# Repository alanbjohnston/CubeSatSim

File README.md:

# CubeSatSim

The CubeSat Simulator https://github.com/alanbjohnston/CubeSatSim/wiki is a low cost satellite emulator that runs on solar panels and batteries, transmits UHF radio telemetry, has a 3D printed frame, and can be extended by additional sensors and modules.  This project is sponsored by the not-for-profit [Radio Amateur Satellite Corporation, AMSAT®](https://amsat.org) https://CubeSatSim.org

The three custom PCBs are the Main, Battery and Solar boards.  Information including schematics and gerbers is in https://CubeSatSim.org/hardware

For information about the AMSAT STEM education program based on the CubeSatSim, see https://CubeSatSim.org/EducatorsGuide

For STEM activities to do with the CubeSatSim, see the https://CubeSatSim.org/ActivityGuides

There are several hardware versions and software branches to go with them - see below for information.

See the Wiki Software Install page for more details: https://github.com/alanbjohnston/CubeSatSim/wiki/2.-Software-Install. The software runs the Raspberry Pi Zero 2W and the Raspberry Pi 4B.  Some of the software runs on a Raspberry Pi 3B, 3B+, Pi Zero, and Pi Zero W.

There are two ways to get the CubeSatSim(TM) software for your Pi.

One option is to download the disk image file and write it to a 16GB micro SD card or larger.  The image is based on Raspberry Pi OS (Bookworm) Legacy. All software is installed, you just need to login to change your password and set your amateur radio callsign if you have one.  You can run the ./update.sh script to update all packages and update and compile the latest CubeSatSim software.

The other option is to start with a Raspberry Pi OS (Rasbian) image (Bookworm Legacy - Trixie is not yet compatible) and run the installation script ./install.sh which will install and compile all the related software.  This includes the following packages:
- wiringpi
- git
- libasound2-dev
- pi-power-button
- Direwolf
- rpitx
- python3-pip
- python3-smbus

## Disk Image Option Steps

See the Wiki Software Install page for details: [https://github.com/alanbjohnston/CubeSatSim/wiki/2.-Software-Install](https://github.com/alanbjohnston/CubeSatSim/wiki/2.-Software-Install#disk-image-option-steps).

## Installation Script Option Steps

Use the Raspberry Pi Imager https://www.raspberrypi.com/software/ and select the Bookworm Legacy option.  Make sure you set your username as pi.  You can also preset your password, localization, and WiFi settings.

       cd
       git clone http://github.com/alanbjohnston/CubeSatSim.git
       cd CubeSatSim
       git checkout master
       ./install

The installation script will run for quite a while.  You will get prompted for your amateur radio callsign in all capitals, if you have one.  If you don't you can put some other word which will be transmitted as a CW ID.  You will also be prompted for your latitude and longitude for APRS packets.  You will need to reboot after the script completes.

Here are some Quick Start Guides for operating the CubeSatSim: https://CubeSatSim.org/qsg

If you want to run the software on a Raspberry Pi Zero or Pi Zero W, you can install it on Bullseye.  Here is a Bullseye Pi OS image that works: https://downloads.raspberrypi.org/raspios_full_armhf/images/raspios_full_armhf-2023-05-03/ Here is the file download link: https://downloads.raspberrypi.org/raspios_full_armhf/images/raspios_full_armhf-2023-05-03/2023-05-03-raspios-bullseye-armhf-full.img.xz

You can use this with the Raspberry Pi Imager, but under `OS` you need to choose the `Use Custom` option at the very bottom of the list, then select the downloaded image `2023-05-03-raspios-bullseye-armhf-full.img.xz`

Unfortunately, Customization is not supported with a Custom image, so you can't preset your username, password, localization, and WiFi settings.

So after you write this image to your microSD card, you will need to connect a monitor and keyboard to your Pi Zero 2 to set these things (make sure you set `pi` as the username). After that, you can connect it to your WiFi and turn on ssh and vnc for remote access.

You can then follow the software installation steps and it work work.  The only hiccup is that if you run the installer script while running the Desktop, the Direwolf installation will freeze.  But you can just cycle the power to the Pi Zero 2, then run the installer script again and it will complete successfully.  Alternatively, if you use `sudo raspi-config` to change to Boot to Console (System/ Boot Auto Login/ Console or Console Auto Login) then the installer script will complete without any issues.

*Note:* CubeSatSim expects to be installed as the `pi` user and references many paths in `/home/pi/*`. Installing as a different user will result in configuration files not saving along with many other issues.

To install the software follow the steps above.

Older Versions

There are several versions of the hardware and software to go with them:

- The original design used a Digital Transceiver Board for the Raspberry Pi (DigitalTxRxRPi) and APRS AFSK 1200 bps telemetry only.  Use the aprs-digitaltxrx branch https://github.com/alanbjohnston/CubeSatSim/tree/aprs-digitaltxrx for this and the vB2 wiki page https://github.com/alanbjohnston/CubeSatSim/wiki/vB2-Home (e.g. run `git checkout aprs-digitaltxrx` before running the ./install.sh script)
- An updated design that used the Transmitter/Filter Board (TFB) instead of the the Transceiver Board.  For the same APRS AFSK telemetry, use the aprs-rpitx branch https://github.com/alanbjohnston/CubeSatSim/tree/aprs-rpitx and the vB3 wiki page https://github.com/alanbjohnston/CubeSatSim/wiki/vB3-Home. (e.g. run `git checkout aprs-rpitx` before running the ./install.sh script) Note that this hardware can still use the master code branch.

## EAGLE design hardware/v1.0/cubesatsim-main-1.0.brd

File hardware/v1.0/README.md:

Here is information about the CubeSatSim v1.0 hardware

Note: this is not the latest hardware!

There are files for the main board, battery board, and STEM payload board of these types:

* cubesatsim-STEM-1.0_gerbers.zip  --    All gerber files used to fabricate PCBs

* cubesatsim-STEM-1.0_schematic.pdf --   Schematic

* cubesatsim-STEM-1.0_board.png     --   View of board

* cubesatsim-STEM-1.0_board_fill.png --  View of board with fill

* cubesatsim-STEM-1.0_topPCB.png    --   Top view of PCB generated by gerbers

* cubesatsim-STEM-1.0_bottomPCB.png  --  Bottom view of PCB generated by gerbers

* cubesatsim-STEM-1.0_tNames.pdf     --  Top outline of components

* cubesatsim-STEM-1.0_bNames.pdf    --   Bottom outline of components

* cubesatsim-STEM-1.0.mnt           --   top SMD component placement data

* cubesatsim-STEM-1.0.mnb           --   bottom SMD component placement data

* cubesatsim-STEM-1.0_bom.csv.txt   --   Bill of Materials in CSV format

I use PCBWay to fabricate PCBs https://pcbway.com

Board sets are available on the AMSAT Store: 
https://www.amsat.org/product/amsat-cubesatsim-pcb/ 

Bill of materials https://CubeSatSim.org/bom 

Instructions https://CubeSatSim.org/wiki

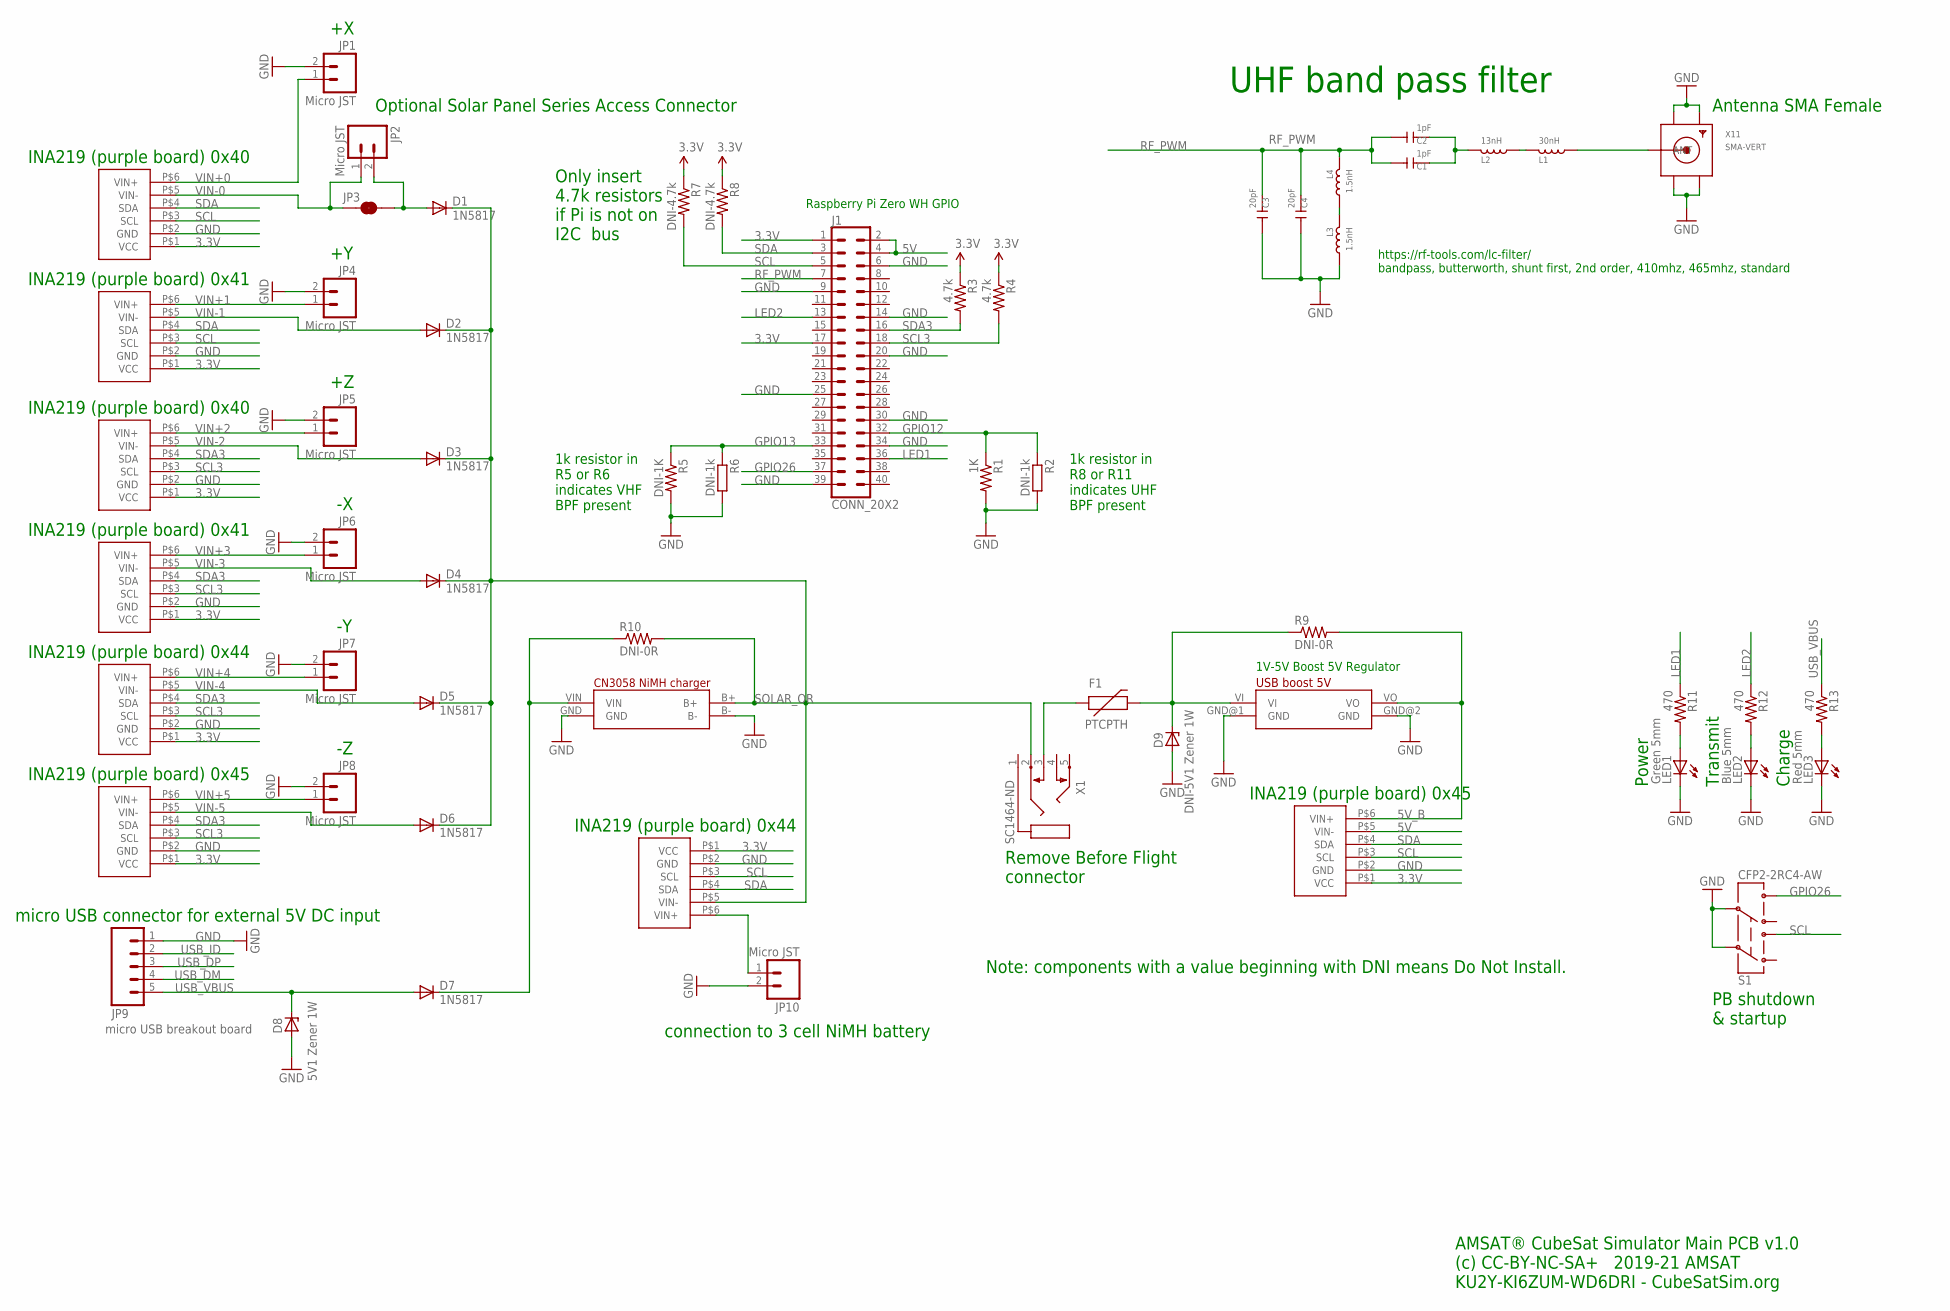
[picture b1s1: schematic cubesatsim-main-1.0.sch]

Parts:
C1, C2: 1pF; C0603
C3, C4: 20pF; C0603
D1, D2, D3, D4, D5, D6, D7: 1N5817; D-2.5
D8: 5V1 Zener 1W; ZDIO-2.5
D9: DNI-5V1 Zener 1W; ZDIO-2.5
F1: PTCPTH; PTC
J1: CONN_20X2; 2X20
JP1, JP2, JP4, JP5, JP6, JP7, JP8, JP10: Micro JST; JST-2-PTH-VERT
JP3: VDD-EN; SMT-JUMPER_2_NC_TRACE_SILK
JP9: micro USB breakout board; 1X05_NO_SILK
L1: 30nH; L0603
L2: 13nH; L0603
L3, L4: 1.5nH; L0603
LED1: Green 5mm; LED3MM
LED2: Blue 5mm; LED3MM
LED3: Red 5mm; LED3MM
R1: 1K; AXIAL-0.1EZ
R2, R6: DNI-1k; R0603
R3, R4: 4.7k; AXIAL-0.1EZ
R5: DNI-1K; AXIAL-0.1EZ
R7, R8: DNI-4.7k; AXIAL-0.1EZ
R9, R10: DNI-0R; AXIAL-0.1EZ
R11, R12, R13: 470; AXIAL-0.1EZ
S1: CFP2-2RC4-AW; OS
U1, U2, U3, U4, U5, U8, U9, U10: INA219 purple board; INA219
U6: CN3085-MODULE
U7: 1V-5V Boost 5V Regulator; USB-BOOST
X1: SC1464-ND; PG203J
X11: SMA-VERT

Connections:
3.3V: J1.1, J1.17, R3.P$1 (1), R4.P$1 (1), R7.P$1 (1), R8.P$1 (1), U1.P$1 (VCC), U2.P$1 (VCC), U3.P$1 (VCC), U4.P$1 (VCC), U5.P$1 (VCC), U8.P$1 (VCC), U9.P$1 (VCC), U10.P$1 (VCC)
5V: J1.2, J1.4, U9.P$5 (VIN-)
5V_B: R9.P$2 (2), U7.VO, U9.P$6 (VIN+)
GND: C3.1, C4.1, D8.A, D9.A, J1.6, J1.9, J1.14, J1.20, J1.25, J1.30, J1.34, J1.39, JP1.2, JP4.2, JP5.2, JP6.2, JP7.2, JP8.2, JP9.1, JP10.2, L3.2, LED1.K (C), LED2.K (C), LED3.K (C), R1.P$2 (2), R2.2, R5.P$2 (2), R6.2, S1.2, S1.5, U1.P$2 (GND), U2.P$2 (GND), U3.P$2 (GND), U4.P$2 (GND), U5.P$2 (GND), U6.B-, U6.GND, U7.GND@1 (GND), U7.GND@2 (GND), U8.P$2 (GND), U9.P$2 (GND), U10.P$2 (GND), X11.GND1, X11.GND2, X11.GND3, X11.GND4
GPIO12: J1.32, R1.P$1 (1), R2.1
GPIO13: J1.33, R5.P$1 (1), R6.1
GPIO26: J1.37, S1.6
LED1: J1.36, R11.P$1 (1)
LED2: J1.13, R12.P$1 (1)
unnamed: D1.A, JP2.2, JP3.2
unnamed: D9.C, F1.P$2 (2), R9.P$1 (1), U7.VI
unnamed: JP10.1, U10.P$6 (VIN+)
unnamed: LED1.A, R11.P$2 (2)
unnamed: F1.P$1 (1), X1.3
unnamed: L1.2, X11.ANTENNA (ANT)
unnamed: LED2.A, R12.P$2 (2)
unnamed: C1.2, C2.2, L2.1
unnamed: LED3.A, R13.P$2 (2)
unnamed: D7.C, R10.P$1 (1), U6.VIN
unnamed: L3.1, L4.2
unnamed: L1.1, L2.2
RF_PWM: C1.1, C2.1, C3.2, C4.2, J1.7, L4.1
SCL: J1.5, R7.P$2 (2), S1.3, U1.P$3 (SCL), U2.P$3 (SCL), U9.P$3 (SCL), U10.P$3 (SCL)
SCL3: J1.18, R4.P$2 (2), U3.P$3 (SCL), U4.P$3 (SCL), U5.P$3 (SCL), U8.P$3 (SCL)
SDA: J1.3, R8.P$2 (2), U1.P$4 (SDA), U2.P$4 (SDA), U9.P$4 (SDA), U10.P$4 (SDA)
SDA3: J1.16, R3.P$2 (2), U3.P$4 (SDA), U4.P$4 (SDA), U5.P$4 (SDA), U8.P$4 (SDA)
SOLAR_OR: D1.C, D2.C, D3.C, D4.C, D5.C, D6.C, R10.P$2 (2), U6.B+, U10.P$5 (VIN-), X1.2
USB_DM: JP9.4
USB_DP: JP9.3
USB_ID: JP9.2
USB_VBUS: D7.A, D8.C, JP9.5, R13.P$1 (1)
VIN+0: JP1.1, U1.P$6 (VIN+)
VIN+1: JP4.1, U2.P$6 (VIN+)
VIN+2: JP5.1, U3.P$6 (VIN+)
VIN+3: JP6.1, U4.P$6 (VIN+)
VIN+4: JP7.1, U5.P$6 (VIN+)
VIN+5: JP8.1, U8.P$6 (VIN+)
VIN-0: JP2.1, JP3.1, U1.P$5 (VIN-)
VIN-1: D2.A, U2.P$5 (VIN-)
VIN-2: D3.A, U3.P$5 (VIN-)
VIN-3: D4.A, U4.P$5 (VIN-)
VIN-4: D5.A, U5.P$5 (VIN-)
VIN-5: D6.A, U8.P$5 (VIN-)

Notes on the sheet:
UHF band pass filter
https://rf-tools.com/lc-filter/ bandpass, butterworth, shunt first, 2nd order, 410mhz, 465mhz, standard
connection to 3 cell NiMH battery
Remove Before Flight connector
micro USB connector for external 5V DC input
PB shutdown & startup
1V-5V Boost 5V Regulator
Raspberry Pi Zero WH GPIO
Power
Charge
Transmit
Antenna SMA Female
AMSAT® CubeSat Simulator Main PCB v1.0 (c) CC-BY-NC-SA+ 2019-21 AMSAT KU2Y-KI6ZUM-WD6DRI - CubeSatSim.org
INA219 (purple board) 0x40
INA219 (purple board) 0x41
INA219 (purple board) 0x44
INA219 (purple board) 0x45
Optional Solar Panel Series Access Connector
Only insert 4.7k resistors if Pi is not on I2C bus
1k resistor in R8 or R11 indicates UHF BPF present
1k resistor in R5 or R6 indicates VHF BPF present
Note: components with a value beginning with DNI means Do Not Install.

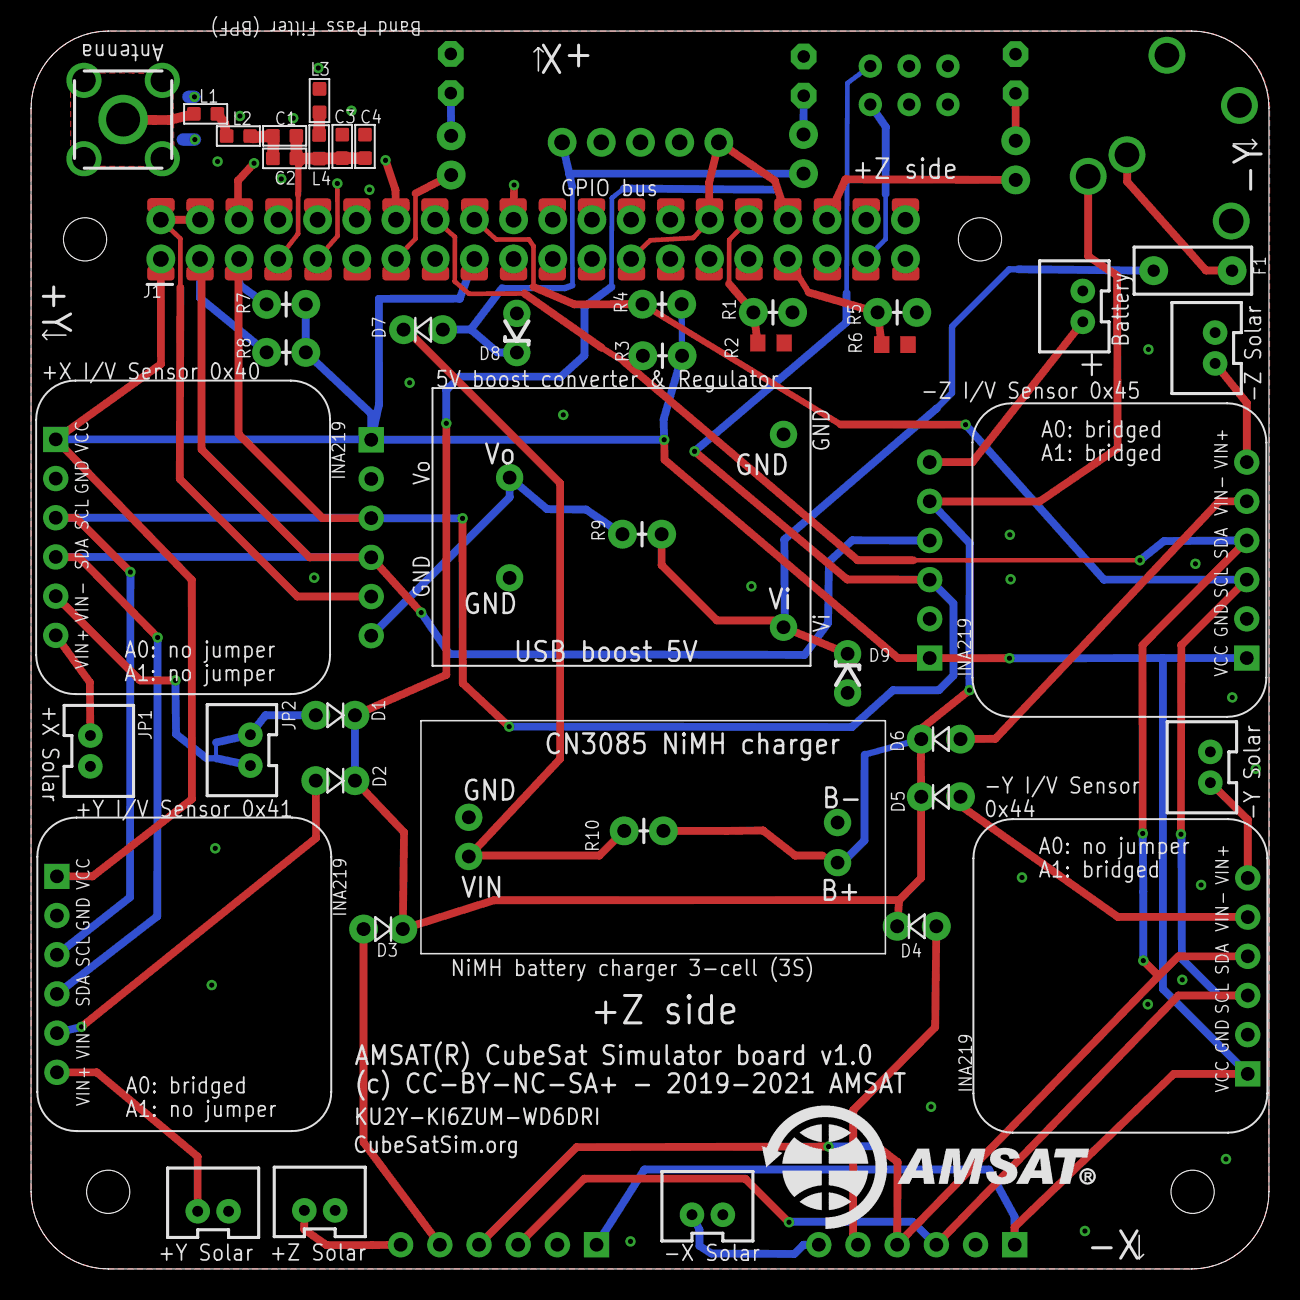
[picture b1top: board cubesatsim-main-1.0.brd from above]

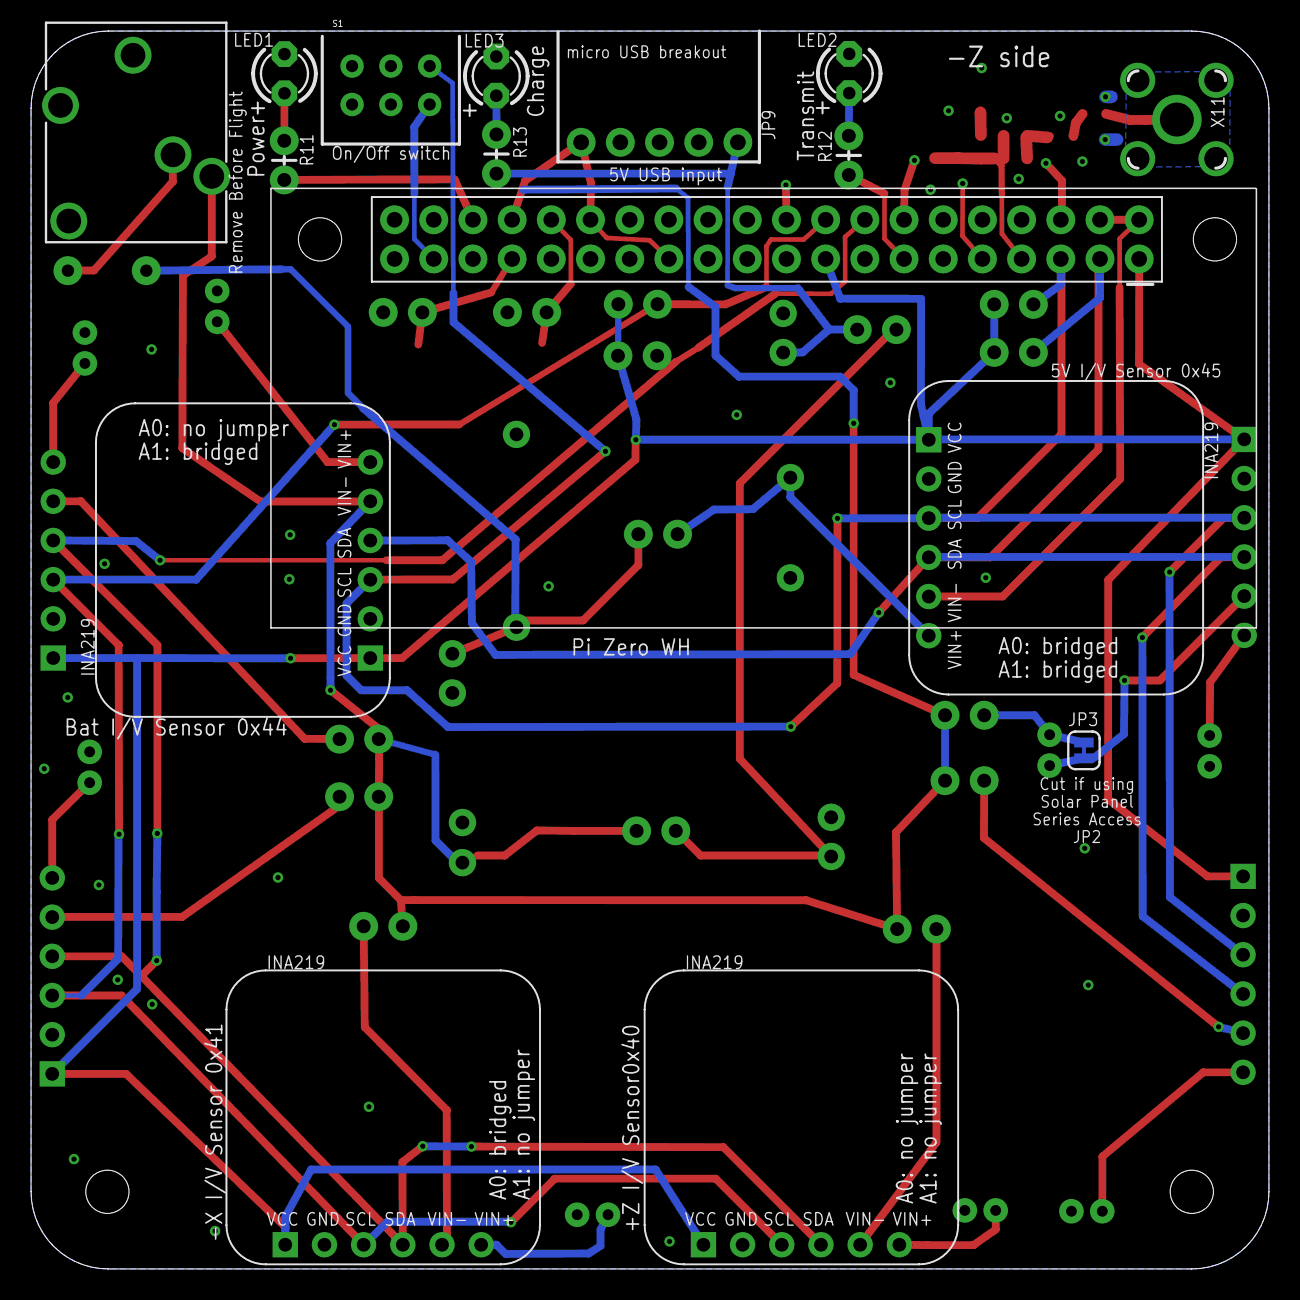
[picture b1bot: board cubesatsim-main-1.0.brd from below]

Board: 2 copper layers, 80.2 x 80.2 mm, 58 parts (15 on the bottom side), 40 nets.

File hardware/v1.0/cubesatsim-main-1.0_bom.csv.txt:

"Qty";"Value";"Device";"Package";"Parts";"Description";"MPN";"VALUE";
"1";"";"CN3085-MODULE";"CN3085-MODULE";"U6";"";"";"";
"2";"1.5nH";"SMD-FERRITE-CHIP-120-OHM-500MA(0603)";"L0603";"L3, L4";"303030001";"BLM18AG121SN1D";"120";
"1";"13nH";"SMD-FERRITE-CHIP-120-OHM-500MA(0603)";"L0603";"L2";"303030001";"BLM18AG121SN1D";"120";
"1";"1K";"RESISTORPTH-1/4W-VERT-KIT";"AXIAL-0.1EZ";"R1";"Resistor";"";"";
"7";"1N5817";"DIODE-D-2.5";"D-2.5";"D1, D2, D3, D4, D5, D6, D7";"DIODE";"";"";
"1";"1V-5V Boost 5V Regulator";"USB-BOOST";"USB-BOOST";"U7";"";"";"";
"2";"1pF";"CERAMIC-10PF-50V-5%-NPO(0603)";"C0603";"C1, C2";"302010097";"";"10pf";
"2";"20pF";"CERAMIC-10PF-50V-5%-NPO(0603)";"C0603";"C3, C4";"302010097";"";"10pf";
"1";"30nH";"SMD-FERRITE-CHIP-120-OHM-500MA(0603)";"L0603";"L1";"303030001";"BLM18AG121SN1D";"120";
"2";"4.7k";"RESISTORPTH-1/4W-VERT-KIT";"AXIAL-0.1EZ";"R3, R4";"Resistor";"";"";
"3";"470";"RESISTORPTH-1/4W-VERT-KIT";"AXIAL-0.1EZ";"R11, R12, R13";"Resistor";"";"";
"1";"5V1 Zener 1W";"ZENER-DIODEZD-2.5";"ZDIO-2.5";"D8";"Z-Diode";"";"";
"1";"Blue 5mm";"LED3MM";"LED3MM";"LED2";"LED";"";"";
"1";"CFP2-2RC4-AW";"SWITCH-DPDTOS";"OS";"S1";"DPDT Version of the COM-00597";"";"";
"1";"CONN_20X2";"CONN_20X2";"2X20";"J1";"Multi connection point. Often used as Generic Header-pin footprint for 0.1 inch spaced/style header connections";"";"";
"2";"DNI-0R";"RESISTORPTH-1/4W-VERT-KIT";"AXIAL-0.1EZ";"R9, R10";"Resistor";"";"";
"1";"DNI-1K";"RESISTORPTH-1/4W-VERT-KIT";"AXIAL-0.1EZ";"R5";"Resistor";"";"";
"2";"DNI-1k";"R-EU_R0603";"R0603";"R2, R6";"RESISTOR, European symbol";"";"";
"2";"DNI-4.7k";"RESISTORPTH-1/4W-VERT-KIT";"AXIAL-0.1EZ";"R7, R8";"Resistor";"";"";
"1";"DNI-5V1 Zener 1W";"ZENER-DIODEZD-2.5";"ZDIO-2.5";"D9";"Z-Diode";"";"";
"1";"Green 5mm";"LED3MM";"LED3MM";"LED1";"LED";"";"";
"8";"INA219 purple board";"INA219";"INA219";"U1, U2, U3, U4, U5, U8, U9, U10";"";"";"";
"8";"Micro JST";"M02JST-PTH-VERT";"JST-2-PTH-VERT";"JP1, JP2, JP4, JP5, JP6, JP7, JP8, JP10";"Standard 2-pin 0.1" header. Use with";"";"";
"1";"PTCPTH";"PTCPTH";"PTC";"F1";"Resettable Fuse PTC";"";"";
"1";"Red 5mm";"LED3MM";"LED3MM";"LED3";"LED";"";"";
"1";"SC1464-ND";"PG203J";"PG203J";"X1";"MIC/HEADPHONE JACK";"";"";
"1";"SMA-VERT";"SMA-VERT";"SMA-VERT";"X11";"";"";"";
"1";"VDD-EN";"JUMPER-SMT_2_NC_TRACE_SILK";"SMT-JUMPER_2_NC_TRACE_SILK";"JP3";"Normally closed trace jumper";"";"";
"1";"micro USB breakout board";"M05NO_SILK";"1X05_NO_SILK";"JP9";"Header 5";"";"";

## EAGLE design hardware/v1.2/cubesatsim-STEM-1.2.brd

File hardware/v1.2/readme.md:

Here is information about the CubeSatSim v1.2 hardware

NOTE: The change between v1.1 and v1.2 is changing the USB charging connector from a micro USB to a USB-C connector. Some labels also changed

There are files for the main board, battery board, and STEM payload board of these types:

* cubesatsim-main-1.2_gerbers.zip  --    All gerber files used to fabricate PCBs

* cubesatsim-main-1.2_schematic.pdf --   Schematic

* cubesatsim-main-1.2_pcb.png     --   View of board

* cubesatsim-main-1.2_board_fill.png --  View of board with fill

* cubesatsim-main-1.2_topPCB.png    --   Top view of PCB generated by gerbers

* cubesatsim-main-1.2_bottomPCB.png  --  Bottom view of PCB generated by gerbers

* cubesatsim-main-1.2_tNames.pdf     --  Top outline of components

* cubesatsim-main-1.2_bNames.pdf    --   Bottom outline of components

* cubesatsim-main-1.2.mnt           --   top SMD component placement data

* cubesatsim-main-1.2.mnb           --   bottom SMD component placement data

* cubesatsim-main-1.2_bom.csv.txt   --   Bill of Materials in CSV format

I use PCBWay to fabricate PCBs https://pcbway.com

Board sets are available on the AMSAT Store: 
https://www.amsat.org/product/amsat-cubesatsim-pcb/ 

Bill of materials https://CubeSatSim.org/bom 

Instructions https://CubeSatSim.org/wiki

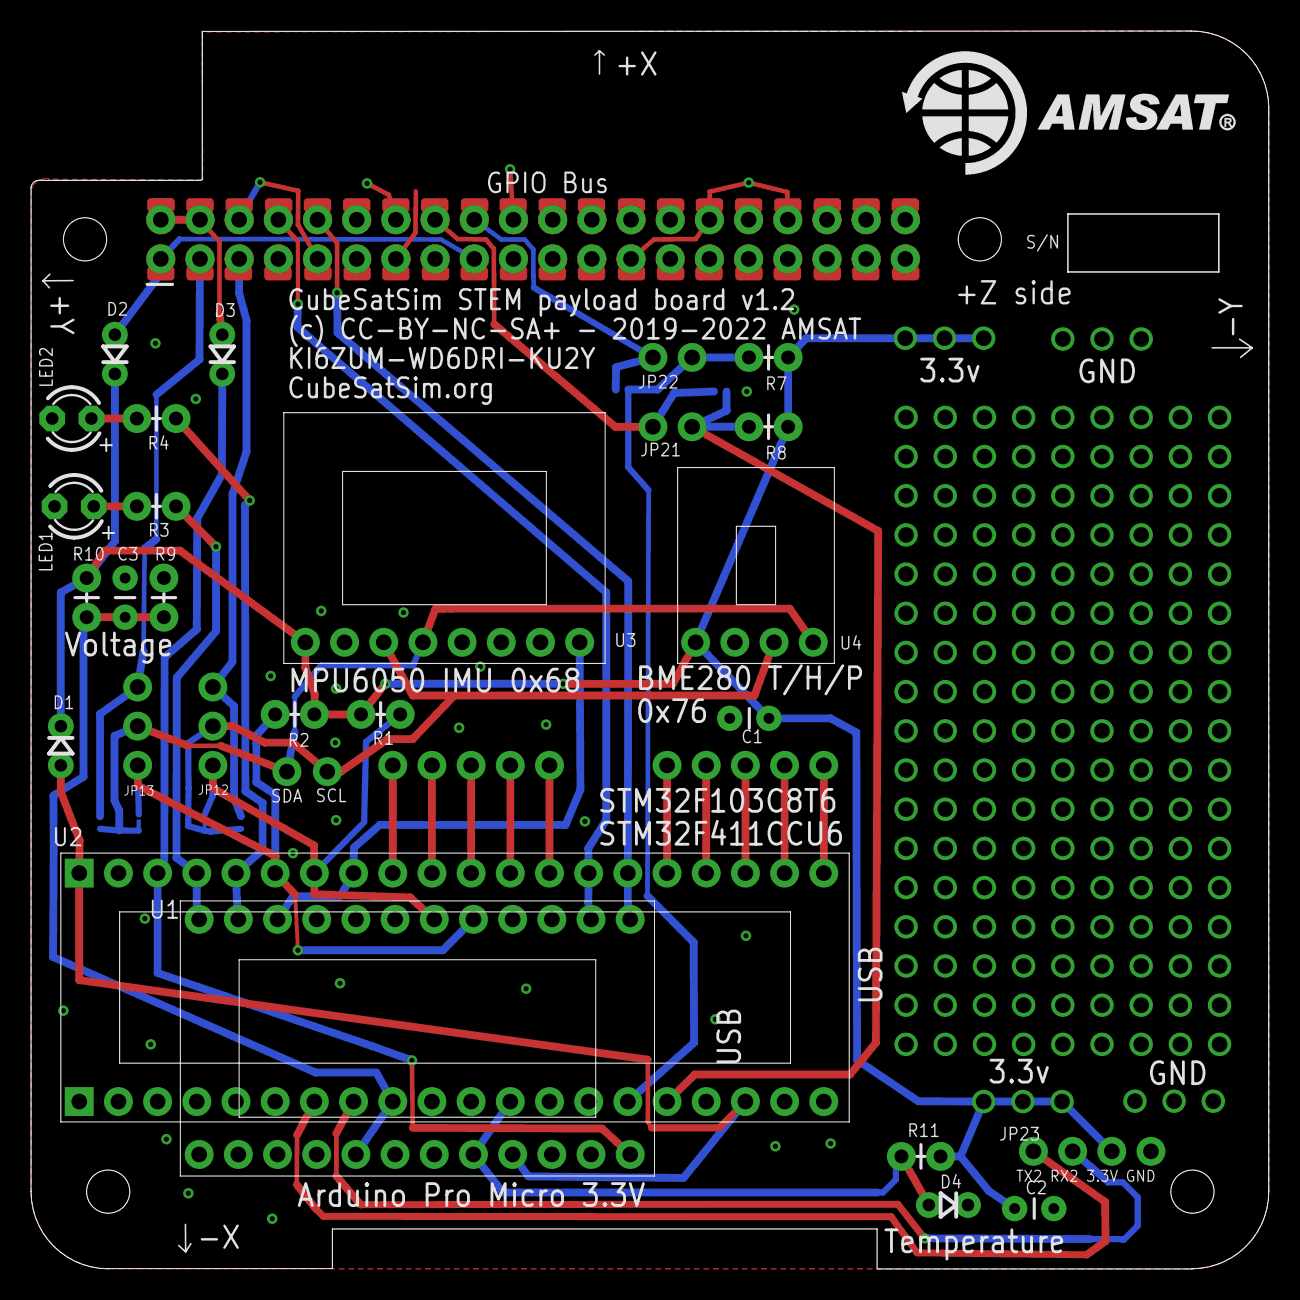
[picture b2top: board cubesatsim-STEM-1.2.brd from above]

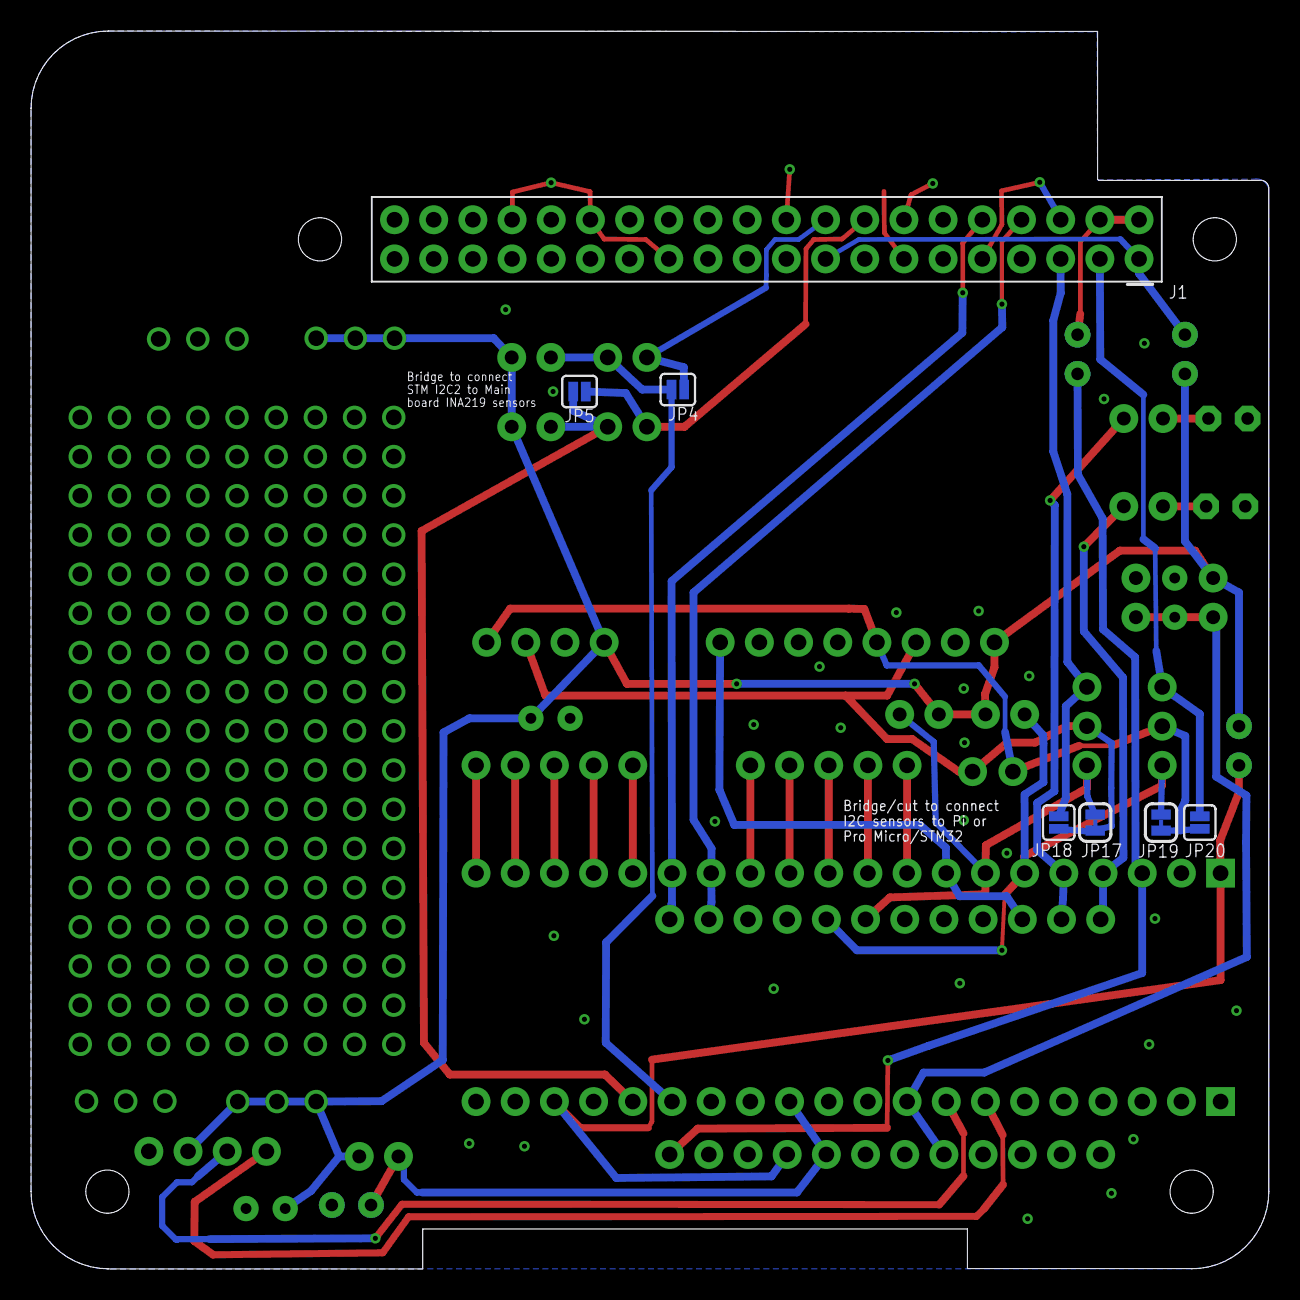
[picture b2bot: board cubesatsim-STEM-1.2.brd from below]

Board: 2 copper layers, 80.2 x 80.2 mm, 47 parts (6 on the bottom side), 37 nets.

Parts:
C1, C2, C3: 100nF; CAP-PTH-SMALL
D1, D2, D3: 1N5817; D-2.5
D4: 1N4148; D-2.5
J1: CONN_20X2; 2X20
JP1, JP2, JP3, JP6, JP7, JP8, JP9, JP10, JP11, JP14, JP15, JP16: 1X01NS-KIT
JP4, JP5, JP18, JP20: JUMPER-SMT_2_NO_SILK; SMT-JUMPER_2_NO_SILK
JP12, JP13: DNI-1x3 pin header with jumper; 1X03_NO_SILK
JP17, JP19: JUMPER-SMT_2_NC_TRACE_SILK; SMT-JUMPER_2_NC_TRACE_SILK
JP21, JP22: DNI-1x2 pin header; 1X02_NO_SILK
JP23: DNI-1x4 pin header; 1X04_NO_SILK
LED1: Green 5mm; LED3MM
LED2: Blue 5mm; LED3MM
R1, R2: 4.7k; AXIAL-0.1
R3: 1k; AXIAL-0.1
R4: 100; AXIAL-0.1
R7, R8: DNI-4k; AXIAL-0.1
R9, R10, R11: 10K; AXIAL-0.1
U1: Sparkfun Pro Micro 3.3V 8MHz; SPARKFUN_PRO_MICRO
U2, U2A: 1x20 female header; 1X20_NOSILK
U3: MPU6050; 1X08_NO_SILK
U4: BME280; 1X04_NO_SILK_ALL_ROUND

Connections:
3.3V: C1.1, C2.1, D1.C, D2.C, JP23.2, R1.P$2, R2.P$2, R7.P$1, R8.P$1, R10.P$1, R11.P$2, U3.8, U4.1
5V: D3.C, U1.24, U2.3
GND: C1.2, C2.2, C3.2, D4.C, J1.6, J1.9, J1.14, J1.20, J1.25, J1.30, J1.34, J1.39, JP23.1, LED1.K, LED2.K, R9.P$2, U1.3, U1.4, U1.23, U2.2, U2A.19, U3.7, U4.2
IMU_INT: U1.10, U2.8, U3.1
unnamed: LED1.A, R3.P$2
unnamed: LED2.A, R4.P$2
PA8: JP14.1, U2.16
PA11: JP3.1, U2.13
PA12: JP7.1, U2.12
PA15: JP6.1, U2.11
PB3: JP8.1, U2.10
PB4: JP9.1, U2.9
PB12: JP10.1, U2.20
PB13: JP11.1, U2.19
PB14: JP15.1, U2.18
PB15: JP16.1, U2.17
PI_3.3V: D2.A, J1.1, J1.17
PI_5V: D3.A, J1.2, J1.4
PI_RXD: J1.10, U1.1, U2.15
PI_SCL: J1.5, JP12.3, JP18.1
PI_SCL3: J1.18, JP4.1, JP22.2
PI_SDA: J1.3, JP13.3, JP20.1
PI_SDA3: J1.16, JP5.1, JP21.2
PI_TXD: J1.8, U1.2, U2.14
RX2: JP23.3, U2A.8
SCL: JP2.1, JP12.2, JP17.1, JP18.2, U3.6, U4.3
SDA: JP1.1, JP13.2, JP19.1, JP20.2, U3.5, U4.4
STM_3.3V: D1.A, U1.21, U2.1, U2A.18
STM_LED1: R3.P$1, U1.12, U2.4
STM_LED2: R4.P$1, U1.11, U2.5
STM_SCL: JP12.1, JP17.2, R1.P$1, U1.6, U2.7
STM_SCL2: JP4.2, JP22.1, R7.P$2, U2A.15
STM_SDA: JP13.1, JP19.2, R2.P$1, U1.5, U2.6
STM_SDA2: JP5.2, JP21.1, R8.P$2, U2A.16
TEMPERATURE: D4.A, R11.P$1, U1.20, U2A.12
TX2: JP23.4, U2A.7
VOLTAGE: C3.1, R9.P$1, R10.P$2, U1.17, U2A.9

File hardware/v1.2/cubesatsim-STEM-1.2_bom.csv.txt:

"Part";"Value";"Device";"Package";"Description";"PROD_ID";
"C1";"100nF";"CAPPTH";"CAP-PTH-SMALL";"Capacitor";"";
"C2";"100nF";"CAPPTH";"CAP-PTH-SMALL";"Capacitor";"";
"C3";"100nF";"CAPPTH";"CAP-PTH-SMALL";"Capacitor";"";
"D1";"1N5817";"DIODE-D-2.5";"D-2.5";"DIODE";"";
"D2";"1N5817";"DIODE-D-2.5";"D-2.5";"DIODE";"";
"D3";"1N5817";"DIODE-D-2.5";"D-2.5";"DIODE";"";
"D4";"1N4148";"DIODE-D-2.5";"D-2.5";"DIODE";"";
"J1";"CONN_20X2";"CONN_20X2";"2X20";"Multi connection point. Often used as Generic Header-pin footprint for 0.1 inch spaced/style header connections";"";
"JP1";"";"M01NOSILK-KIT";"1X01NS-KIT";"Header 1";"";
"JP2";"";"M01NOSILK-KIT";"1X01NS-KIT";"Header 1";"";
"JP3";"";"M01NOSILK-KIT";"1X01NS-KIT";"Header 1";"";
"JP4";"JUMPER-SMT_2_NO_SILK";"JUMPER-SMT_2_NO_SILK";"SMT-JUMPER_2_NO_SILK";"Normally open jumper";"";
"JP5";"JUMPER-SMT_2_NO_SILK";"JUMPER-SMT_2_NO_SILK";"SMT-JUMPER_2_NO_SILK";"Normally open jumper";"";
"JP6";"";"M01NOSILK-KIT";"1X01NS-KIT";"Header 1";"";
"JP7";"";"M01NOSILK-KIT";"1X01NS-KIT";"Header 1";"";
"JP8";"";"M01NOSILK-KIT";"1X01NS-KIT";"Header 1";"";
"JP9";"";"M01NOSILK-KIT";"1X01NS-KIT";"Header 1";"";
"JP10";"";"M01NOSILK-KIT";"1X01NS-KIT";"Header 1";"";
"JP11";"";"M01NOSILK-KIT";"1X01NS-KIT";"Header 1";"";
"JP12";"DNI-1x3 pin header with jumper";"M031X03_NO_SILK";"1X03_NO_SILK";"Header 3";"";
"JP13";"DNI-1x3 pin header with jumper";"M031X03_NO_SILK";"1X03_NO_SILK";"Header 3";"";
"JP14";"";"M01NOSILK-KIT";"1X01NS-KIT";"Header 1";"";
"JP15";"";"M01NOSILK-KIT";"1X01NS-KIT";"Header 1";"";
"JP16";"";"M01NOSILK-KIT";"1X01NS-KIT";"Header 1";"";
"JP17";"JUMPER-SMT_2_NC_TRACE_SILK";"JUMPER-SMT_2_NC_TRACE_SILK";"SMT-JUMPER_2_NC_TRACE_SILK";"Normally closed trace jumper";"";
"JP18";"JUMPER-SMT_2_NO_SILK";"JUMPER-SMT_2_NO_SILK";"SMT-JUMPER_2_NO_SILK";"Normally open jumper";"";
"JP19";"JUMPER-SMT_2_NC_TRACE_SILK";"JUMPER-SMT_2_NC_TRACE_SILK";"SMT-JUMPER_2_NC_TRACE_SILK";"Normally closed trace jumper";"";
"JP20";"JUMPER-SMT_2_NO_SILK";"JUMPER-SMT_2_NO_SILK";"SMT-JUMPER_2_NO_SILK";"Normally open jumper";"";
"JP21";"DNI-1x2 pin header";"CONN_021X02_NO_SILK";"1X02_NO_SILK";"Multi connection point. Often used as Generic Header-pin footprint for 0.1 inch spaced/style header connections";"";
"JP22";"DNI-1x2 pin header";"CONN_021X02_NO_SILK";"1X02_NO_SILK";"Multi connection point. Often used as Generic Header-pin footprint for 0.1 inch spaced/style header connections";"";
"JP23";"DNI-1x4 pin header";"CONN_041X04_NO_SILK";"1X04_NO_SILK";"Multi connection point. Often used as Generic Header-pin footprint for 0.1 inch spaced/style header connections";"CONN-09696";
"LED1";"Green 5mm";"LED3MM";"LED3MM";"LED";"";
"LED2";"Blue 5mm";"LED3MM";"LED3MM";"LED";"";
"LED3";"DNI-Green 5mm";"LED3MM";"LED3MM";"LED";"";
"LED4";"DNI-Blue 5mm";"LED3MM";"LED3MM";"LED";"";
"R1";"4.7k";"RESISTORPTH-1/4W-VERT";"AXIAL-0.1";"Resistor";"";
"R2";"4.7k";"RESISTORPTH-1/4W-VERT";"AXIAL-0.1";"Resistor";"";
"R3";"470";"RESISTORPTH-1/4W-VERT";"AXIAL-0.1";"Resistor";"";
"R4";"470";"RESISTORPTH-1/4W-VERT";"AXIAL-0.1";"Resistor";"";
"R5";"DNI-1k";"RESISTORPTH-1/4W-VERT";"AXIAL-0.1";"Resistor";"";
"R6";"DNI-100";"RESISTORPTH-1/4W-VERT";"AXIAL-0.1";"Resistor";"";
"R7";"DNI-4k";"RESISTORPTH-1/4W-VERT";"AXIAL-0.1";"Resistor";"";
"R8";"DNI-4k";"RESISTORPTH-1/4W-VERT";"AXIAL-0.1";"Resistor";"";
"R9";"10K";"RESISTORPTH-1/4W-VERT";"AXIAL-0.1";"Resistor";"";
"R10";"10K";"RESISTORPTH-1/4W-VERT";"AXIAL-0.1";"Resistor";"";
"R11";"10K";"RESISTORPTH-1/4W-VERT";"AXIAL-0.1";"Resistor";"";
"U1";"Sparkfun Pro Micro 3.3V 8MHz";"SPARKFUN_PRO_MICRO";"SPARKFUN_PRO_MICRO";"SparkFun Pro Micro";"";
"U2";"1x20 female header";"M20NOSILK";"1X20_NOSILK";"1x20 .1" header";"";
"U2A";"1x20 female header";"M20NOSILK";"1X20_NOSILK";"1x20 .1" header";"";
"U3";"MPU6050";"M08NO_SILK_FEMALE_PTH";"1X08_NO_SILK";"Header 8";"CONN-08438";
"U4";"BME280";"M04NO_SILK_ALL_ROUND";"1X04_NO_SILK_ALL_ROUND";"Header 4";"";

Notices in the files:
hardware/v1.0/cubesatsim-main-1.0.brd:
(c) CC-BY-NC-SA+ - 2019-2021 AMSAT
hardware/v1.2/cubesatsim-STEM-1.2.brd:
(c) CC-BY-NC-SA+ - 2019-2022 AMSAT
parts and their libraries:
SparkFun-Connectors: Licensing: CC v3.0 Share-Alike You are welcome to use this library for commercial purposes.
SparkFun-PowerIC: Licensing: Creative Commons ShareAlike 4.0 International - https://creativecommons.org/licenses/by-sa/4.0
